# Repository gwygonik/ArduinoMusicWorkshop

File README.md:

# ArduinoMusicWorkshop
Arduino code, 3D models, and PCBs for Making Music with Arduino Workshop

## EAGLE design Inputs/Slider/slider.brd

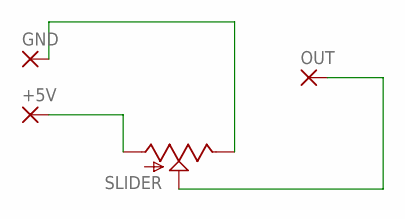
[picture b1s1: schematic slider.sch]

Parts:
+5V: 2,54/1,1
GND: 2,54/1,1
OUT: 2,54/1,1
SLIDER: SLIDER20MM; SLIDER-SMALL

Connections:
unnamed: +5V.1, SLIDER.BOTTOM (A)
unnamed: GND.1, SLIDER.TOP (E)
unnamed: OUT.1, SLIDER.WIPER (S)

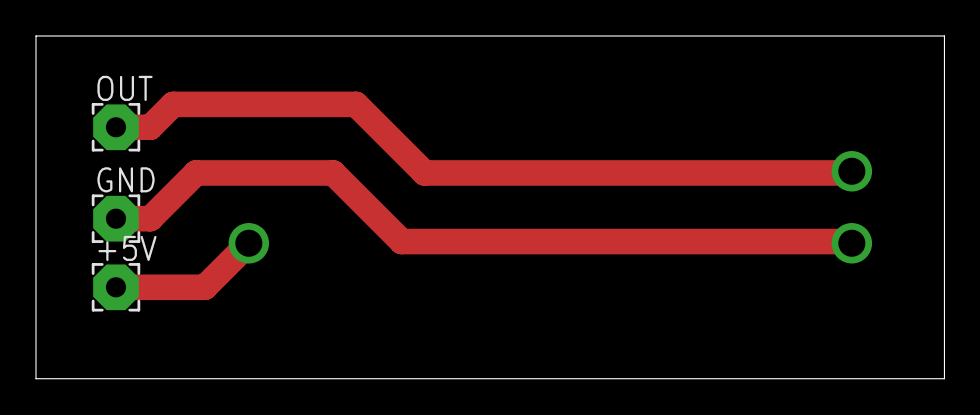
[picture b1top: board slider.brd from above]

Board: 2 copper layers, 50.5 x 19.0 mm, 4 parts (1 on the bottom side), 3 nets.

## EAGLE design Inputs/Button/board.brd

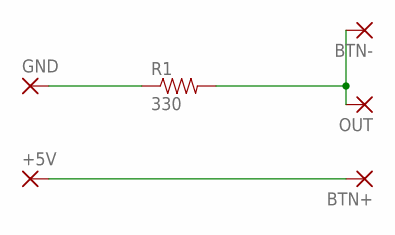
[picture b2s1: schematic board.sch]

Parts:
+5V: 2,54/1,0
BTN+: 2,54/1,0
BTN-: 2,54/1,0
GND: 2,54/1,0
OUT: 2,54/1,0
R1: 330; AXIAL-0.4

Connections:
unnamed: GND.1, R1.P$1 (1)
unnamed: BTN-.1, OUT.1, R1.P$2 (2)
unnamed: +5V.1, BTN+.1

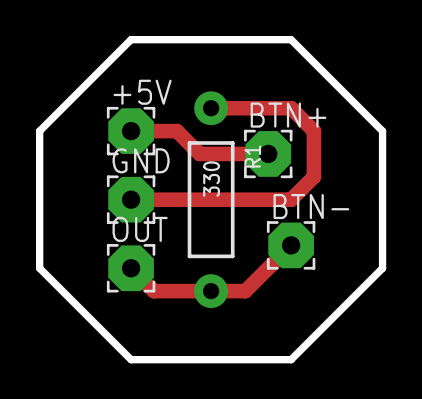
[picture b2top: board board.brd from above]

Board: 2 copper layers, 19.1 x 17.8 mm, 6 parts (0 on the bottom side), 3 nets.

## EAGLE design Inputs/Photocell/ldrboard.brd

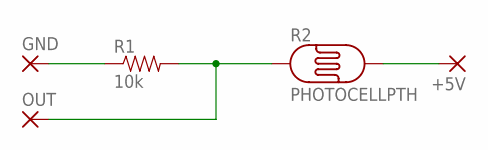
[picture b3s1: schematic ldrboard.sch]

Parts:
+5V: 2,54/1,1
GND: 2,54/1,1
OUT: 2,54/1,1
R1: 10k; AXIAL-0.3
R2: PHOTOCELLPTH; PHOTOCELL

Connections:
unnamed: OUT.1, R1.P$2 (2), R2.1
unnamed: GND.1, R1.P$1 (1)
unnamed: +5V.1, R2.2

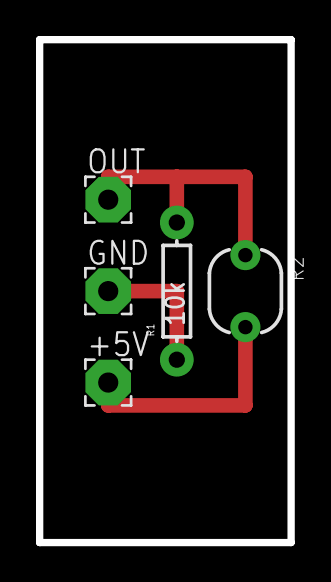
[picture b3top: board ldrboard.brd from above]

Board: 2 copper layers, 14.0 x 27.9 mm, 5 parts (0 on the bottom side), 3 nets.

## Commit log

2015-05-05 Initial Commit
    These are all the files for my Arduino Music Workshop
2015-05-05 Initial commit of deck
    deck deck deck deck!

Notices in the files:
parts and their libraries:
SparkFun-Resistors: Licensing: Creative Commons ShareAlike 4.0 International - https://creativecommons.org/licenses/by-sa/4.0
